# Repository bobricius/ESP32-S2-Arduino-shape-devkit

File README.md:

# ESP32-S2-Arduino-shape-devkit
Simplified Adafruit Metro ESP32-S2

ESP32-S2 development board.

Tested:

0.96" IPS display

#Circuitpython

Arduino IDE

DFU Bootloader

PCB Made in 

@AislerHQ www.aisler.net
 
Thanks 
@adafruit for great work!

Simplified Metro board.

DISPLAY:

  #define TFT_CS         7

  #define TFT_RST        5

  #define TFT_DC         6

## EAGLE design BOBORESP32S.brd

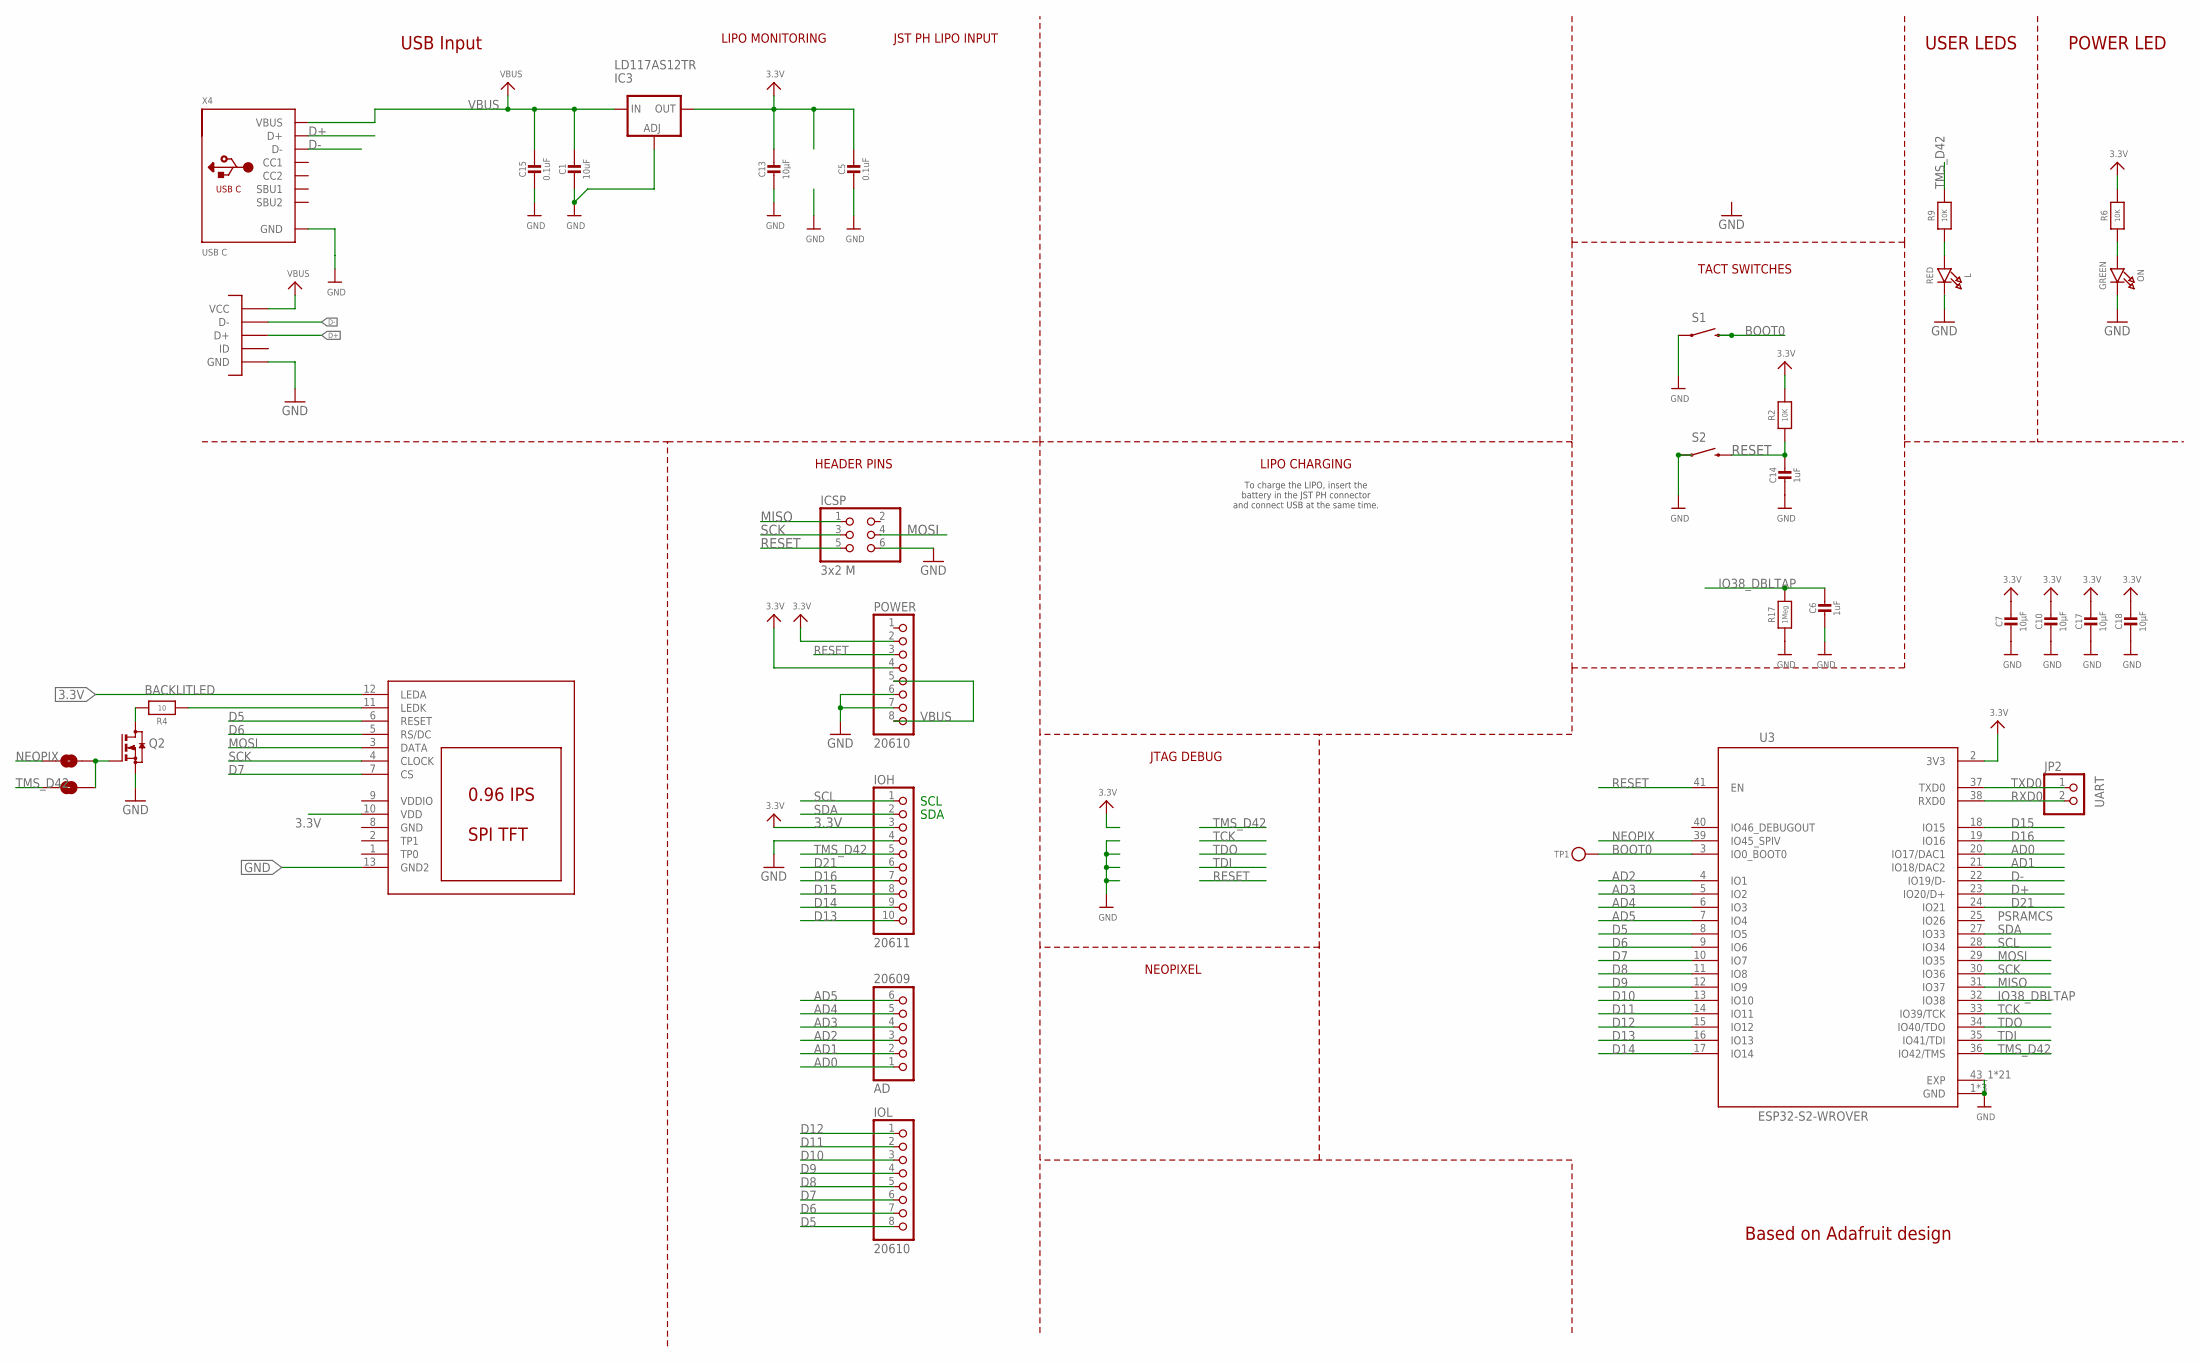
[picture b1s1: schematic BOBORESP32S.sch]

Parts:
AD: 20609; 1X06_OVALWAVE
C1: 10uF; _0805
C5: 0.1uF; _0805
C6, C14: 1uF; _0603
C7, C10, C13, C17, C18: 10µF; _0805
C15: 0.1uF; _0603
IC3: LD117AS12TR; SOT223
ICSP: 3x2 M; 2X03_ROUND_70MIL
IOH: 20611; 1X10_OVALWAVE
IOL: 20610; 1X08_OVALWAVE
JP2: UART; 1X02_ROUND
JUMPER1: SOLDERJUMPERTRACE; SJ_2S-TRACE
JUMPER2: SOLDERJUMPERNC2; SJ_2S-NOTRACE
L: RED; CHIPLED_0603_NOOUTLINE
ON: GREEN; CHIPLED_0603_NOOUTLINE
POWER: 20610; 1X08_OVALWAVE
Q2: BSS123; SOT23
R2, R6, R9: 10K; 0603-NO
R4: 10; 0603-NO
R17: 1Meg; 0603-NO
S1, S2: SWITCH-MOMENTARY-2PTH; TACTILE-PTH
TP1: TESTPOINTROUND1.5MMNO; TESTPOINT_ROUND_1.5MM_NO
U3: ESP32-S2-WROVER; MODULE_ESP32-S2-WROVER
U$5: MICROUSB; MICRO_B
U$9: DISP_LCD_0.9IN_160X80; TFT_0.96IN_160X80B
X4: USB C; USB_C_CUSB31-CFM2AX-01-X

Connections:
3.3V: C5.1, C7.1, C10.1, C13.1, C17.1, C18.1, IC3.4 (OUT), IOH.3, POWER.2, POWER.4, R2.2, R6.2, U3.2 (3V3), U$9.10 (VDD), U$9.12 (LEDA)
AD0: AD.1, U3.20 (IO17/DAC1)
AD1: AD.2, U3.21 (IO18/DAC2)
AD2: AD.3, U3.4 (IO1)
AD3: AD.4, U3.5 (IO2)
AD4: AD.5, U3.6 (IO3)
AD5: AD.6, U3.7 (IO4)
BACKLITLED: R4.1, U$9.11 (LEDK)
BOOT0: S1.3 (2), TP1.P$1, U3.3 (IO0_BOOT0)
D5: IOL.8, U3.8 (IO5), U$9.6 (RESET)
D6: IOL.7, U3.9 (IO6), U$9.5 (RS/DC)
D7: IOL.6, U3.10 (IO7), U$9.7 (CS)
D8: IOL.5, U3.11 (IO8)
D9: IOL.4, U3.12 (IO9)
D10: IOL.3, U3.13 (IO10)
D11: IOL.2, U3.14 (IO11)
D12: IOL.1, U3.15 (IO12)
D13: IOH.10, U3.16 (IO13)
D14: IOH.9, U3.17 (IO14)
D15: IOH.8, U3.18 (IO15)
D16: IOH.7, U3.19 (IO16)
D21: IOH.6, U3.24 (IO21)
D+: U3.23 (IO20/D+), U$5.P3 (D+), X4.A6 (D+), X4.B6 (D+)
D-: U3.22 (IO19/D-), U$5.P2 (D-), X4.A7 (D-), X4.B7 (D-)
DISPBL: JUMPER1.1, JUMPER2.1, Q2.1 (G)
GND: C1.2, C5.2, C6.2, C7.2, C10.2, C13.2, C14.2, C15.2, C17.2, C18.2, IC3.1 (ADJ), ICSP.6, IOH.4, L.C, ON.C, POWER.6, POWER.7, Q2.2 (S), R17.1, S1.1, S2.1, U3.1 (GND), U3.26 (GND), U3.42 (GND), U3.43_1 (EXP), U3.43_2 (EXP), U3.43_3 (EXP), U3.43_4 (EXP), U3.43_5 (EXP), U3.43_6 (EXP), U3.43_7 (EXP), U3.43_8 (EXP), U3.43_9 (EXP), U3.43_10 (EXP), U3.43_11 (EXP), U3.43_12 (EXP), U3.43_13 (EXP), U3.43_14 (EXP), U3.43_15 (EXP), U3.43_16 (EXP), U3.43_17 (EXP), U3.43_18 (EXP), U3.43_19 (EXP), U3.43_20 (EXP), U3.43_21 (EXP), U$5.GND1 (GND), U$5.GND2 (GND), U$5.GND3 (GND), U$5.GND4 (GND), U$5.GND7 (GND), U$5.GND8 (GND), U$5.P5 (GND), U$9.8 (GND), U$9.13 (GND2), X4.A1B12 (GND), X4.B1A12 (GND)
IO38_DBLTAP: C6.1, R17.2, U3.32 (IO38)
MISO: ICSP.1, U3.31 (IO37)
MOSI: ICSP.4, U3.29 (IO35), U$9.3 (DATA)
unnamed: L.A, R9.1
unnamed: Q2.3 (D), R4.2
unnamed: ON.A, R6.1
NEOPIX: JUMPER2.2, U3.39 (IO45_SPIV)
RESET: C14.1, ICSP.5, POWER.3, R2.1, S2.3 (2), U3.41 (EN)
RXD0: JP2.2, U3.38 (RXD0)
SCK: ICSP.3, U3.30 (IO36), U$9.4 (CLOCK)
SCL: IOH.1, U3.28 (IO34)
SDA: IOH.2, U3.27 (IO33)
TCK: U3.33 (IO39/TCK)
TDI: U3.35 (IO41/TDI)
TDO: U3.34 (IO40/TDO)
TMS_D42: IOH.5, JUMPER1.2, R9.2, U3.36 (IO42/TMS)
TXD0: JP2.1, U3.37 (TXD0)
VBUS: C1.1, C15.1, IC3.3 (IN), POWER.5, POWER.8, U$5.P1 (VCC), X4.A4B9 (VBUS), X4.B4A9 (VBUS)
VDDIO: U$9.9 (VDDIO)

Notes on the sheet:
SDA
SCL
Based on Adafruit design
USB Input
POWER LED
USER LEDS
LIPO CHARGING
LIPO MONITORING
To charge the LIPO, insert the battery in the JST PH connector and connect USB at the same time.
JST PH LIPO INPUT
HEADER PINS
TACT SWITCHES
JTAG DEBUG
NEOPIXEL
PSRAMCS

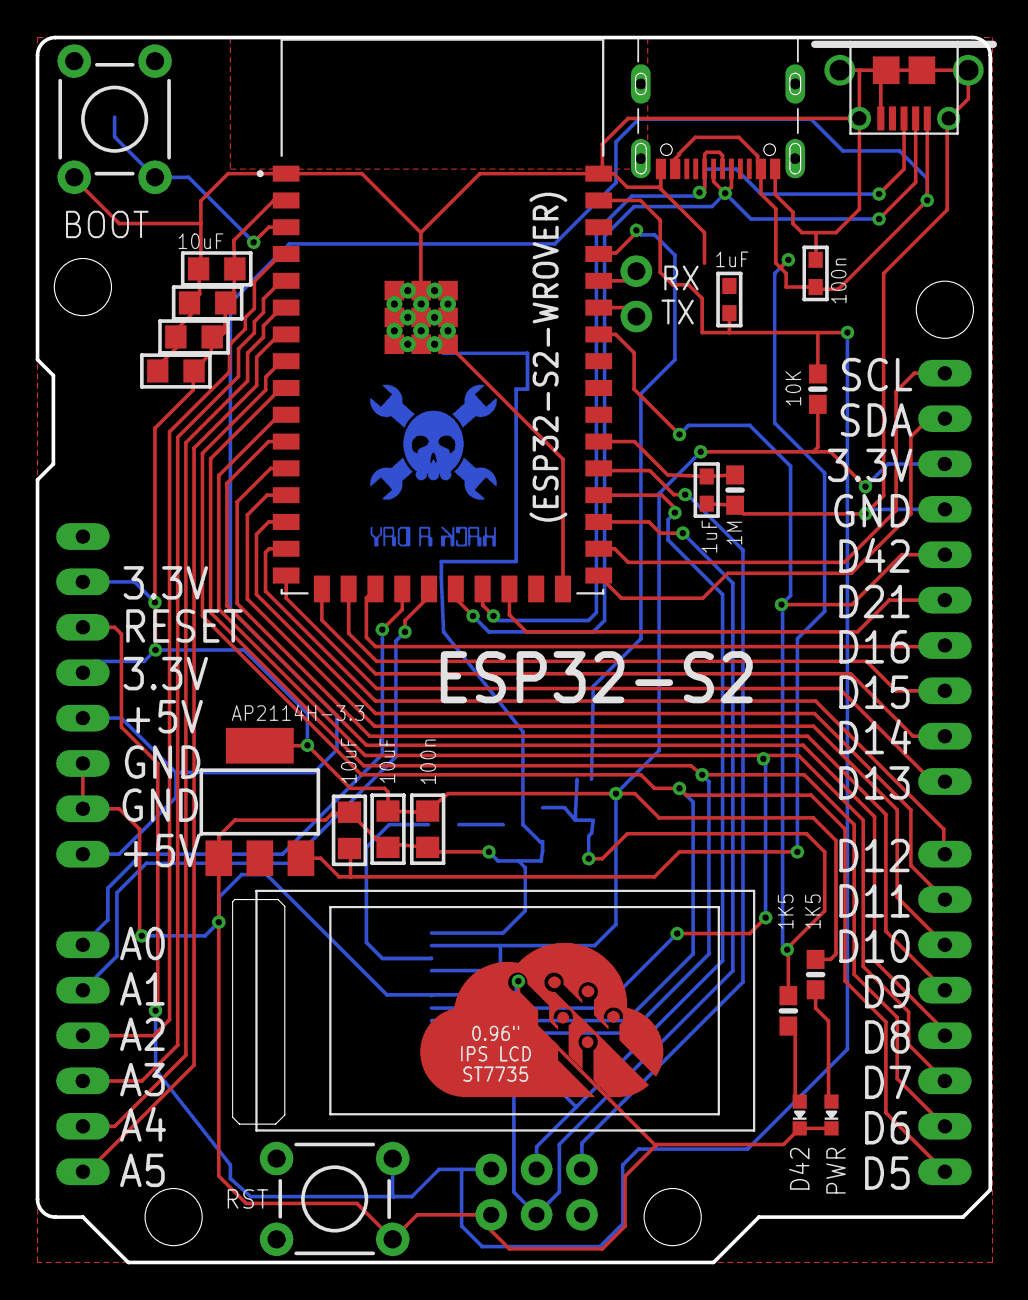
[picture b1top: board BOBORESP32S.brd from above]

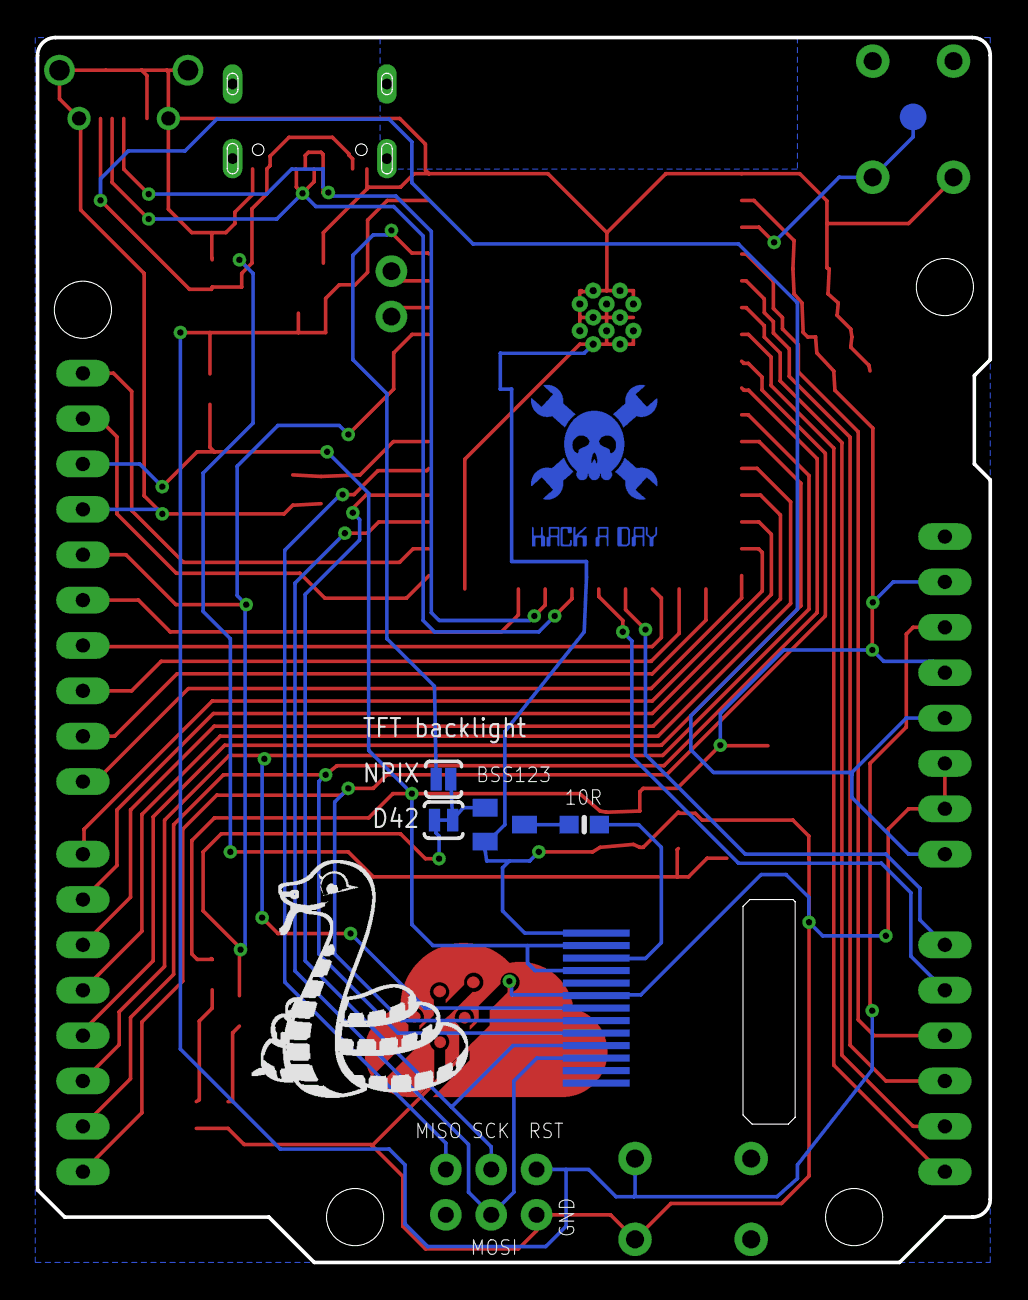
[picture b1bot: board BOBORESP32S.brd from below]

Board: 2 copper layers, 53.3 x 68.6 mm, 34 parts (5 on the bottom side), 41 nets.

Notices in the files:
parts and their libraries:
microbuilder: This work is placed in the public domain, and may be freely used for commercial and non-commercial work with the following conditions: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
SparkFun-Electromechanical: Licensing: Creative Commons ShareAlike 4.0 International - https://creativecommons.org/licenses/by-sa/4.0
